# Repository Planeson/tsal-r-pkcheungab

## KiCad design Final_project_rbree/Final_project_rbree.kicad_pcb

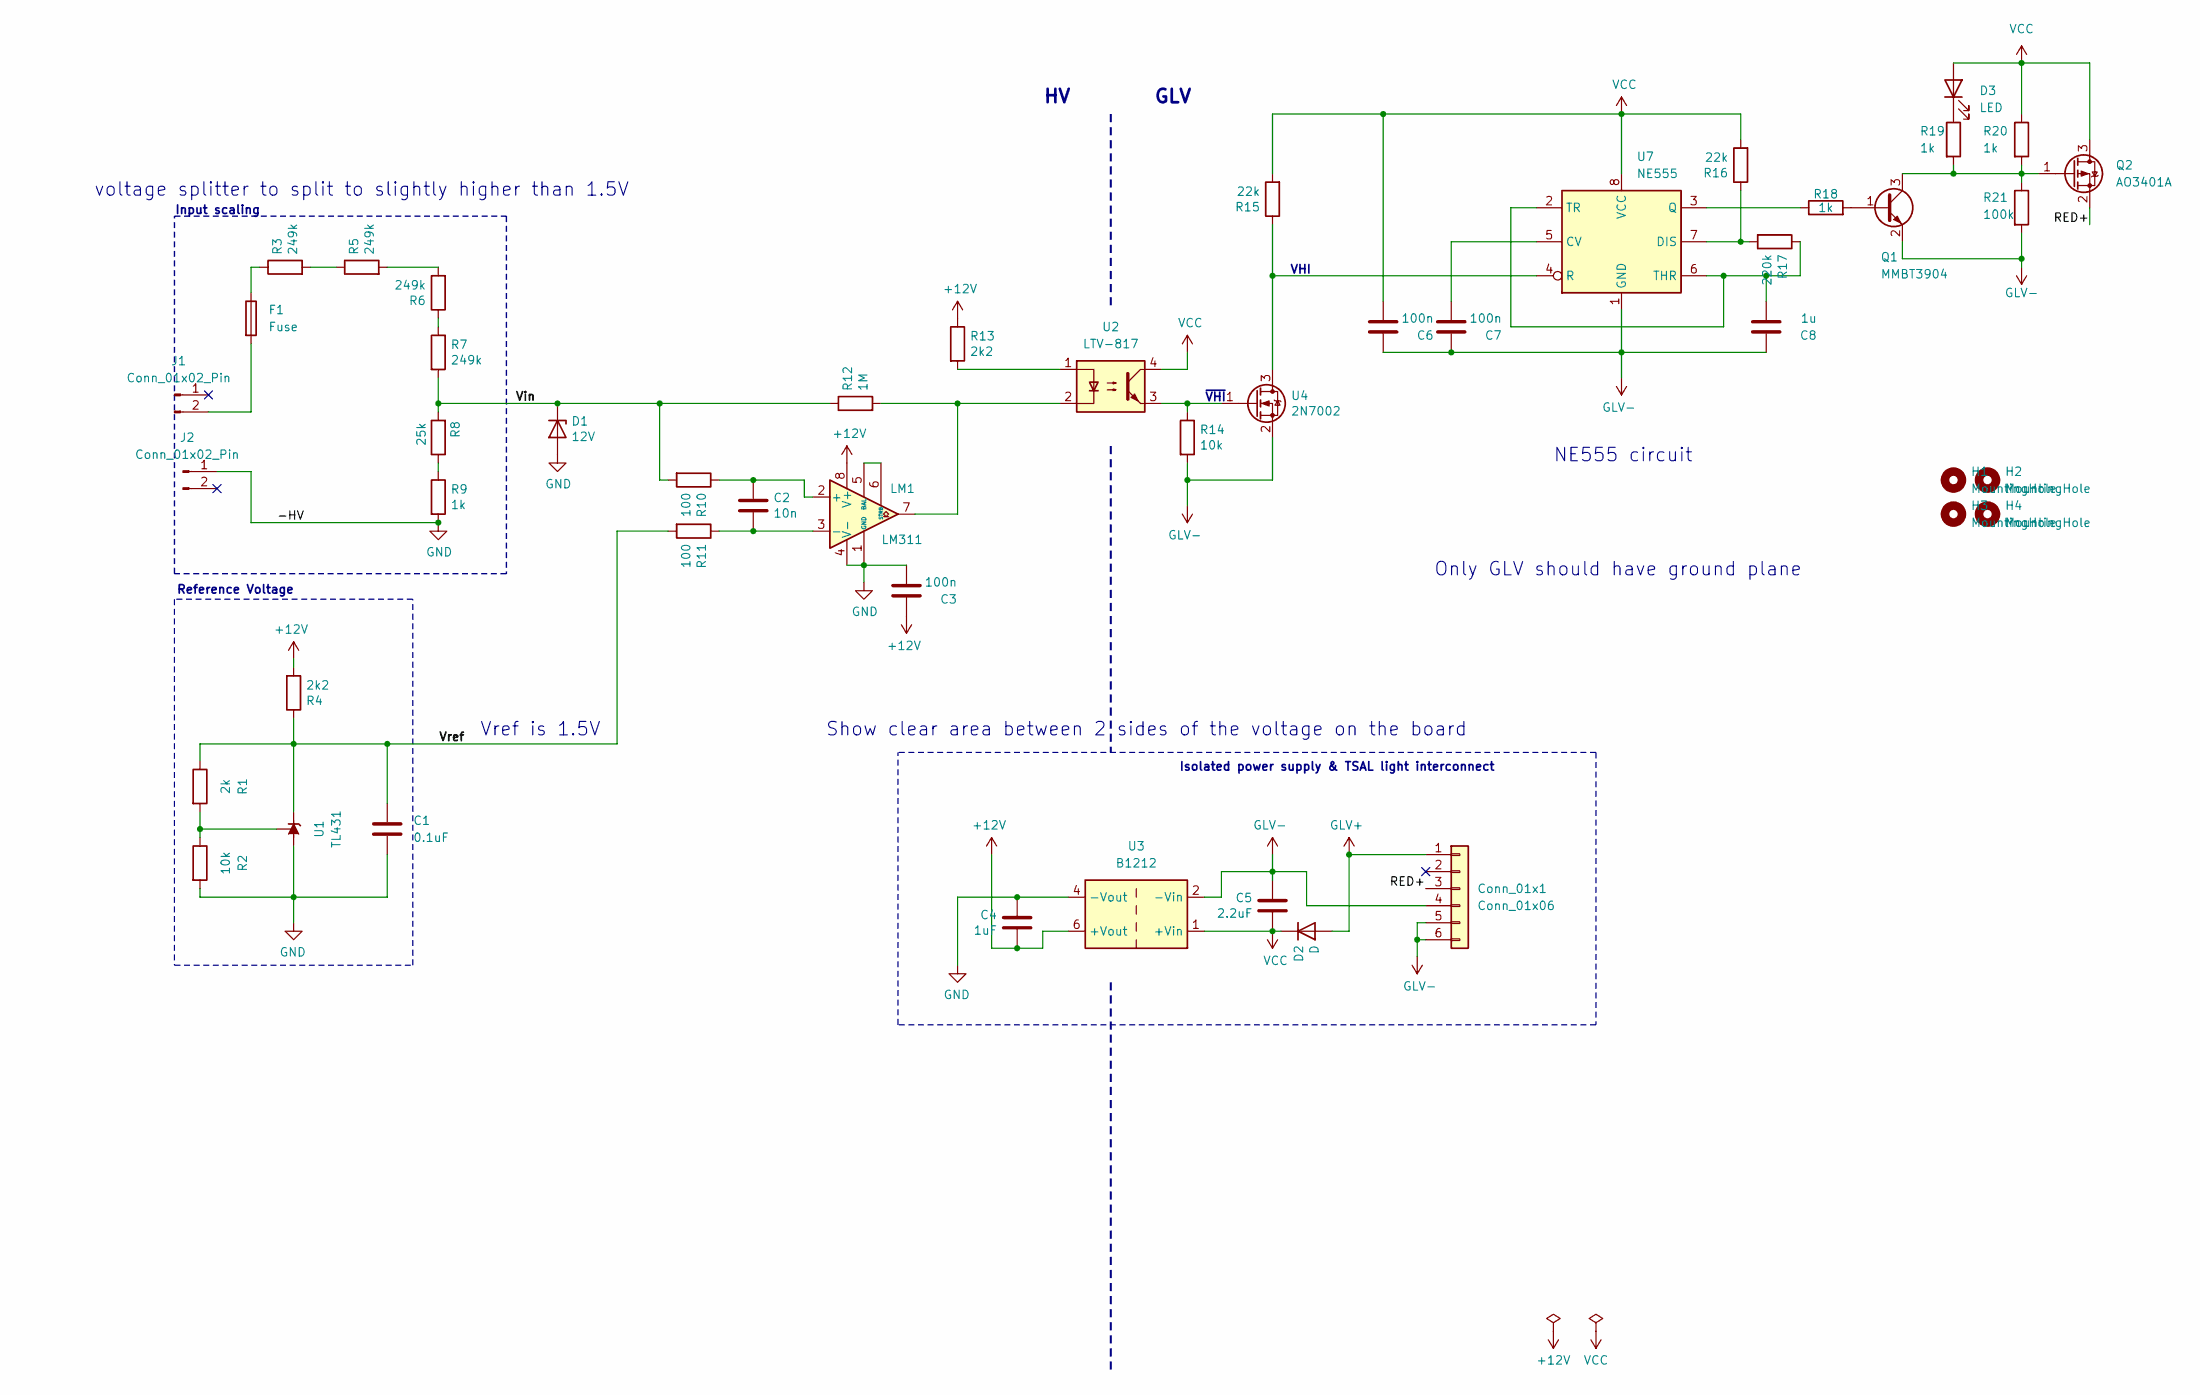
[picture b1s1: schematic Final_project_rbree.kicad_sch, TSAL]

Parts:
C1: 0.1uF; C_1206_3216Metric_Pad1.33x1.80mm_HandSolder
C2: 10n; C_1206_3216Metric_Pad1.33x1.80mm_HandSolder
C3, C6, C7: 100n; C_1206_3216Metric_Pad1.33x1.80mm_HandSolder
C4: 1uF; C_1206_3216Metric_Pad1.33x1.80mm_HandSolder
C5: 2.2uF; C_1206_3216Metric_Pad1.33x1.80mm_HandSolder
C8: 1u; C_1206_3216Metric_Pad1.33x1.80mm_HandSolder
Conn_01x1: Conn_01x06; JST_VH_B6P-VH_1x06_P3.96mm_Vertical
D1: 12V; D_DO-35_SOD27_P7.62mm_Horizontal
D2: D; D_SMA_Handsoldering
D3: LED; LED_1206_3216Metric_Pad1.42x1.75mm_HandSolder
F1: Fuse; Fuse_1206_3216Metric_Pad1.42x1.75mm_HandSolder
H1, H2, H3, H4: MountingHole; MountingHole_3.2mm_M3
J1, J2: Conn_01x02_Pin; AMASS_XT60-M_1x02_P7.20mm_Vertical
LM1: LM311; SOIC-8_3.9x4.9mm_P1.27mm
Q1: MMBT3904; SOT-23
Q2: AO3401A; SOT-23
R1: 2k; R_1206_3216Metric_Pad1.30x1.75mm_HandSolder
R2, R14: 10k; R_1206_3216Metric_Pad1.30x1.75mm_HandSolder
R3, R5, R6, R7: 249k; R_1206_3216Metric_Pad1.30x1.75mm_HandSolder
R4, R13: 2k2; R_1206_3216Metric_Pad1.30x1.75mm_HandSolder
R8: 25k; R_1206_3216Metric_Pad1.30x1.75mm_HandSolder
R9, R18, R19, R20: 1k; R_1206_3216Metric_Pad1.30x1.75mm_HandSolder
R10, R11: 100; R_1206_3216Metric_Pad1.30x1.75mm_HandSolder
R12: 1M; R_1206_3216Metric_Pad1.30x1.75mm_HandSolder
R15, R16: 22k; R_1206_3216Metric_Pad1.30x1.75mm_HandSolder
R17: 220k; R_1206_3216Metric_Pad1.30x1.75mm_HandSolder
R21: 100k; R_1206_3216Metric_Pad1.30x1.75mm_HandSolder
U1: TL431; SOT-23
U2: LTV-817; DIP-4_W8.89mm_SMDSocket_LongPads
U3: B1212; Converter_DCDC_TRACO_TBA2-xxxx_Single_THT
U4: 2N7002; SOT-23
U7: NE555; SOIC-8_3.9x4.9mm_P1.27mm

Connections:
+12V: C3.1, C4.2, LM1.8 (V+), R4.2, R13.1, U3.6 (+Vout)
/RED+: Conn_01x1.3, Q2.2 (S)
/Vin: D1.1 (K), R7.2, R8.2, R10.2, R12.1
/Vref: C1.1, R1.1, R4.1, R11.2, U1.3 (K)
GLV+: Conn_01x1.1, D2.2 (A)
GLV-: C5.1, C6.1, C7.1, C8.1, Conn_01x1.4, Conn_01x1.5, Conn_01x1.6, Q1.2 (E), R14.2, R21.2, U3.2 (-Vin), U4.2 (S), U7.1 (GND)
GND: C1.2, C3.2, C4.1, D1.2 (A), J2.1, LM1.1 (GND), LM1.4 (V-), R2.2, R9.2, U1.2 (A), U3.4 (-Vout)
unnamed: D3.1 (K), R19.1
unnamed: F1.1, R3.1
unnamed: F1.2, J1.2
unnamed: C2.1, LM1.2 (+), R10.1
unnamed: C2.2, LM1.3 (-), R11.1
unnamed: LM1.5 (BAL), LM1.6 (STRB)
unnamed: LM1.7, R12.2, U2.2
unnamed: Q1.1 (B), R18.2
unnamed: Q1.3 (C), Q2.1 (G), R19.2, R20.2, R21.1
unnamed: R3.2, R5.1
unnamed: R5.2, R6.2
unnamed: R6.1, R7.1
unnamed: R8.1, R9.1
unnamed: R13.2, U2.1
unnamed: R1.2, R2.1, U1.1 (REF)
unnamed: R15.1, U4.3 (D), U7.4 (R)
unnamed: R14.1, U2.3, U4.1 (G)
unnamed: C7.2, U7.5 (CV)
unnamed: R16.1, R17.2, U7.7 (DIS)
unnamed: R18.1, U7.3 (Q)
unnamed: C8.2, R17.1, U7.2 (TR), U7.6 (THR)
VCC: C5.2, C6.2, D2.1 (K), D3.2 (A), Q2.3 (D), R15.2, R16.2, R20.1, U2.4, U3.1 (+Vin), U7.8 (VCC)

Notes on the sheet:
voltage splitter to split to slightly higher than 1.5V
Show clear area between 2 sides of the voltage on the board
Isolated power supply & TSAL light interconnect
Reference Voltage
~{VHI}
Input scaling
Only GLV should have ground plane
GLV
VHI
Vref is 1.5V
NE555 circuit

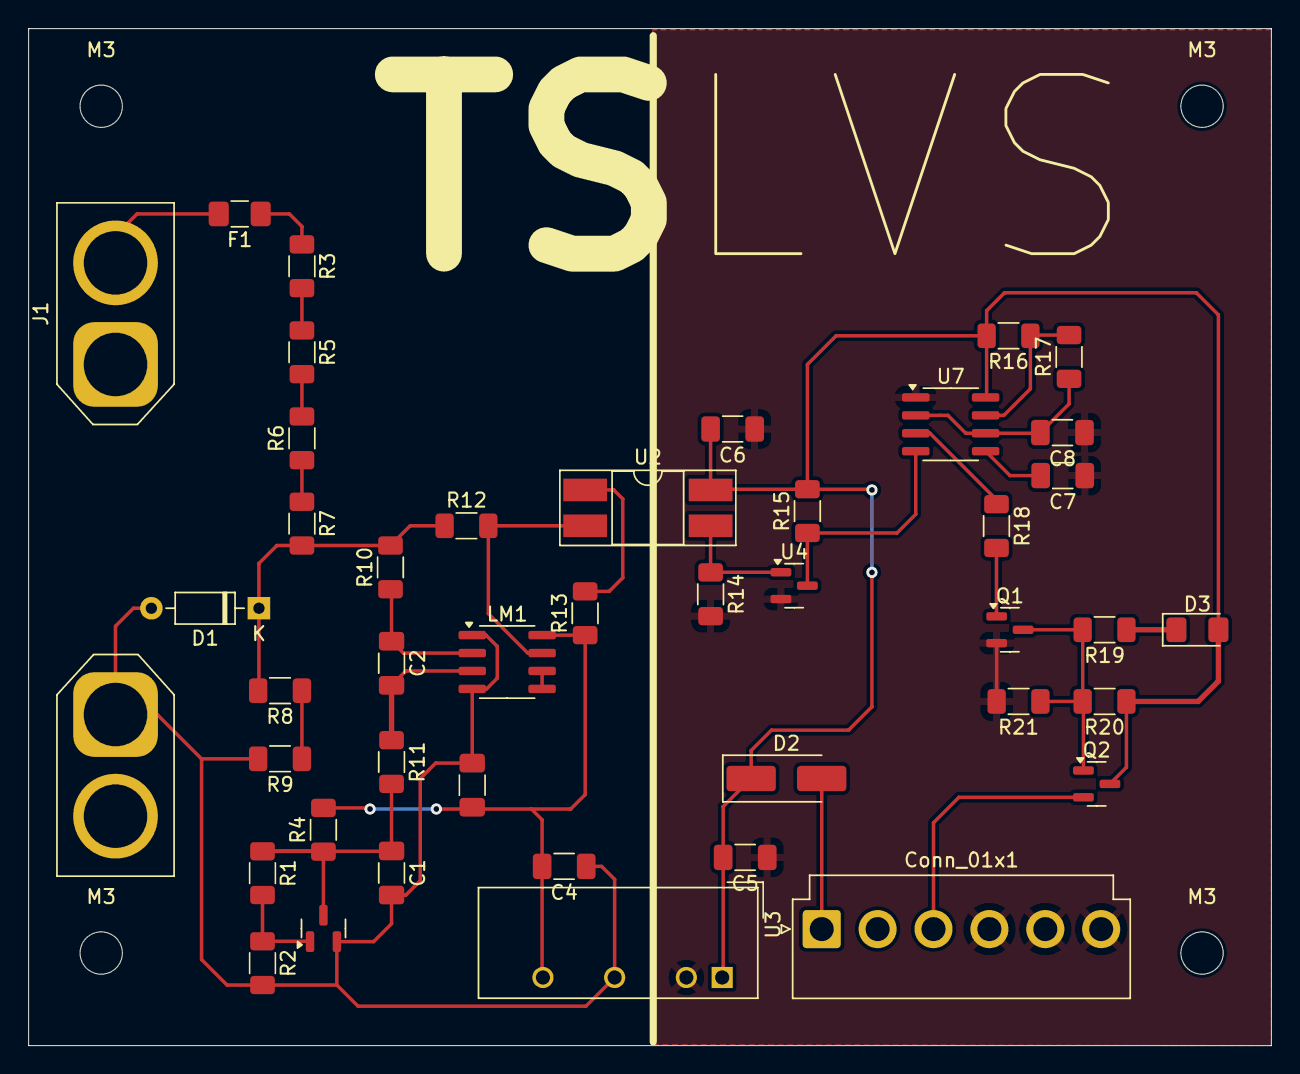
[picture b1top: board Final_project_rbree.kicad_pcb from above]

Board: 2 copper layers, 88.1 x 72.1 mm, 48 parts (0 on the bottom side), 29 nets.

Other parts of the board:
M3, M3#2, M3#3, M3#4: MountingHole; MountingHole_3mm

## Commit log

2025-01-24 Initial Version
    Unfinished
2025-01-26 First version
    First version, completed design
2025-01-30 PCB Redesign 1
    Moved components on board to save space;
    Screw holes 3mm apart;
    Moved filters to better locations
2025-02-03 Added B.Cu, Silkscreen
2025-02-04 Post-interview build
    Slightly rewired PCB, schematics still have changes to be made.
